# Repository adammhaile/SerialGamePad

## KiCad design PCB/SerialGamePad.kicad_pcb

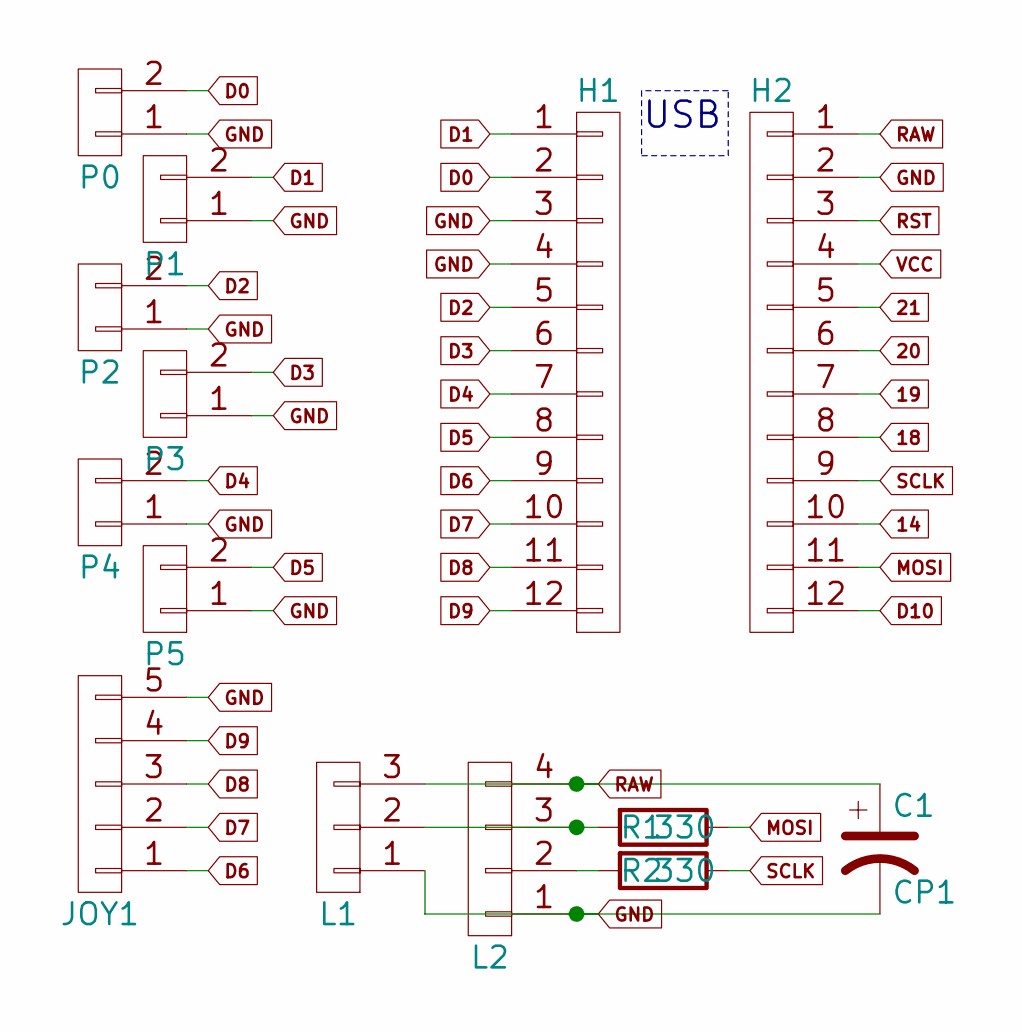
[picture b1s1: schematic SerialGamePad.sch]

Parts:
C1: CP1
H1, H2: CONN_01X12; 1x12_offset
JOY1: CONN_01X05; 1x5_offset
L1: CONN_01X03; 1x3_offset
L2: CONN_01X04; 1x4_offset
P0, P1, P2, P3, P4, P5: CONN_01X02; Arcade_1x2
R1, R2: 330; RC03

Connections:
14: H2.10
18: H2.8
19: H2.7
20: H2.6
21: H2.5
D0: H1.2, P0.2
D1: H1.1, P1.2
D2: H1.5, P2.2
D3: H1.6, P3.2
D4: H1.7, P4.2
D5: H1.8, P5.2
D6: H1.9, JOY1.1
D7: H1.10, JOY1.2
D8: H1.11, JOY1.3
D9: H1.12, JOY1.4
D10: H2.12
GND: C1.2, H1.3, H1.4, H2.2, JOY1.5, L1.1, L2.1, P0.1, P1.1, P2.1, P3.1, P4.1, P5.1
MOSI: H2.11, R1.1
unnamed: L1.2, L2.3, R1.2
unnamed: L2.2, R2.2
RAW: C1.1, H2.1, L1.3, L2.4
RST: H2.3
SCLK: H2.9, R2.1
VCC: H2.4

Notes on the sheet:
USB

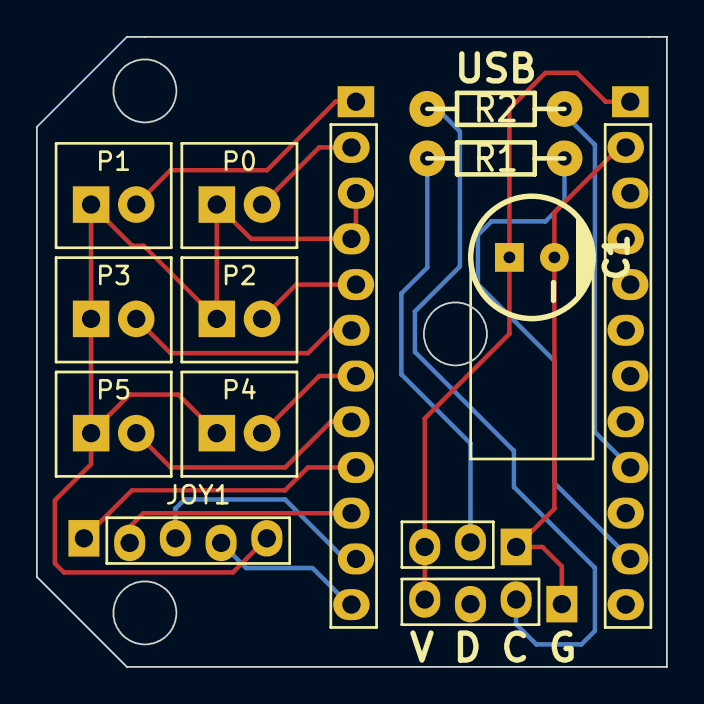
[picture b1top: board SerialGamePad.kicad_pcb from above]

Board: 2 copper layers, 35.0 x 35.0 mm, 14 parts (0 on the bottom side), 16 nets.

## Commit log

2015-06-28 :space_invader: Added .gitattributes & .gitignore files
2015-06-28 Testing out games
2015-07-27 fixing autosaves
